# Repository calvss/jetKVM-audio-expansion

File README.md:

# JetKVM compatible audio ADC
This project takes in mic/line level audio from the 3.5mm jack and digitizes it using a Raspberry Pi Pico 2.

The audio is sent through the serial interface in a modified 48kHz 16-bit 2-channel PCM format. The audio is sent in packets of 32768 samples each, with a `0xFFFF` stop character at the end to ensure left/right channel alignment.

The JetKVM reads its serial interface from `/dev/ttyS3` and sends the raw byte packets though the network to a client PC running a python script (`test_piping.py`) that decodes the packets into a standard PCM audio stream.

## How to deploy:

Since the JetKVM doesn't ship with scp by default, we can use ssh and pipe the binary manually: `cat build/audio-client-c | ssh root@jetKVM "cat > /root/audio-client-c"`

## How to use:

On the client: `ssh root@jetkvm "/root/audio-client-c" | ffplay -fflags nobuffer -f s16le -ch_layout stereo -ar 48k -`.

# Known issues:
If you're going to fab this board design you should know the tip and sleeve contacts on the 3.5mm jack footprint are backwards.

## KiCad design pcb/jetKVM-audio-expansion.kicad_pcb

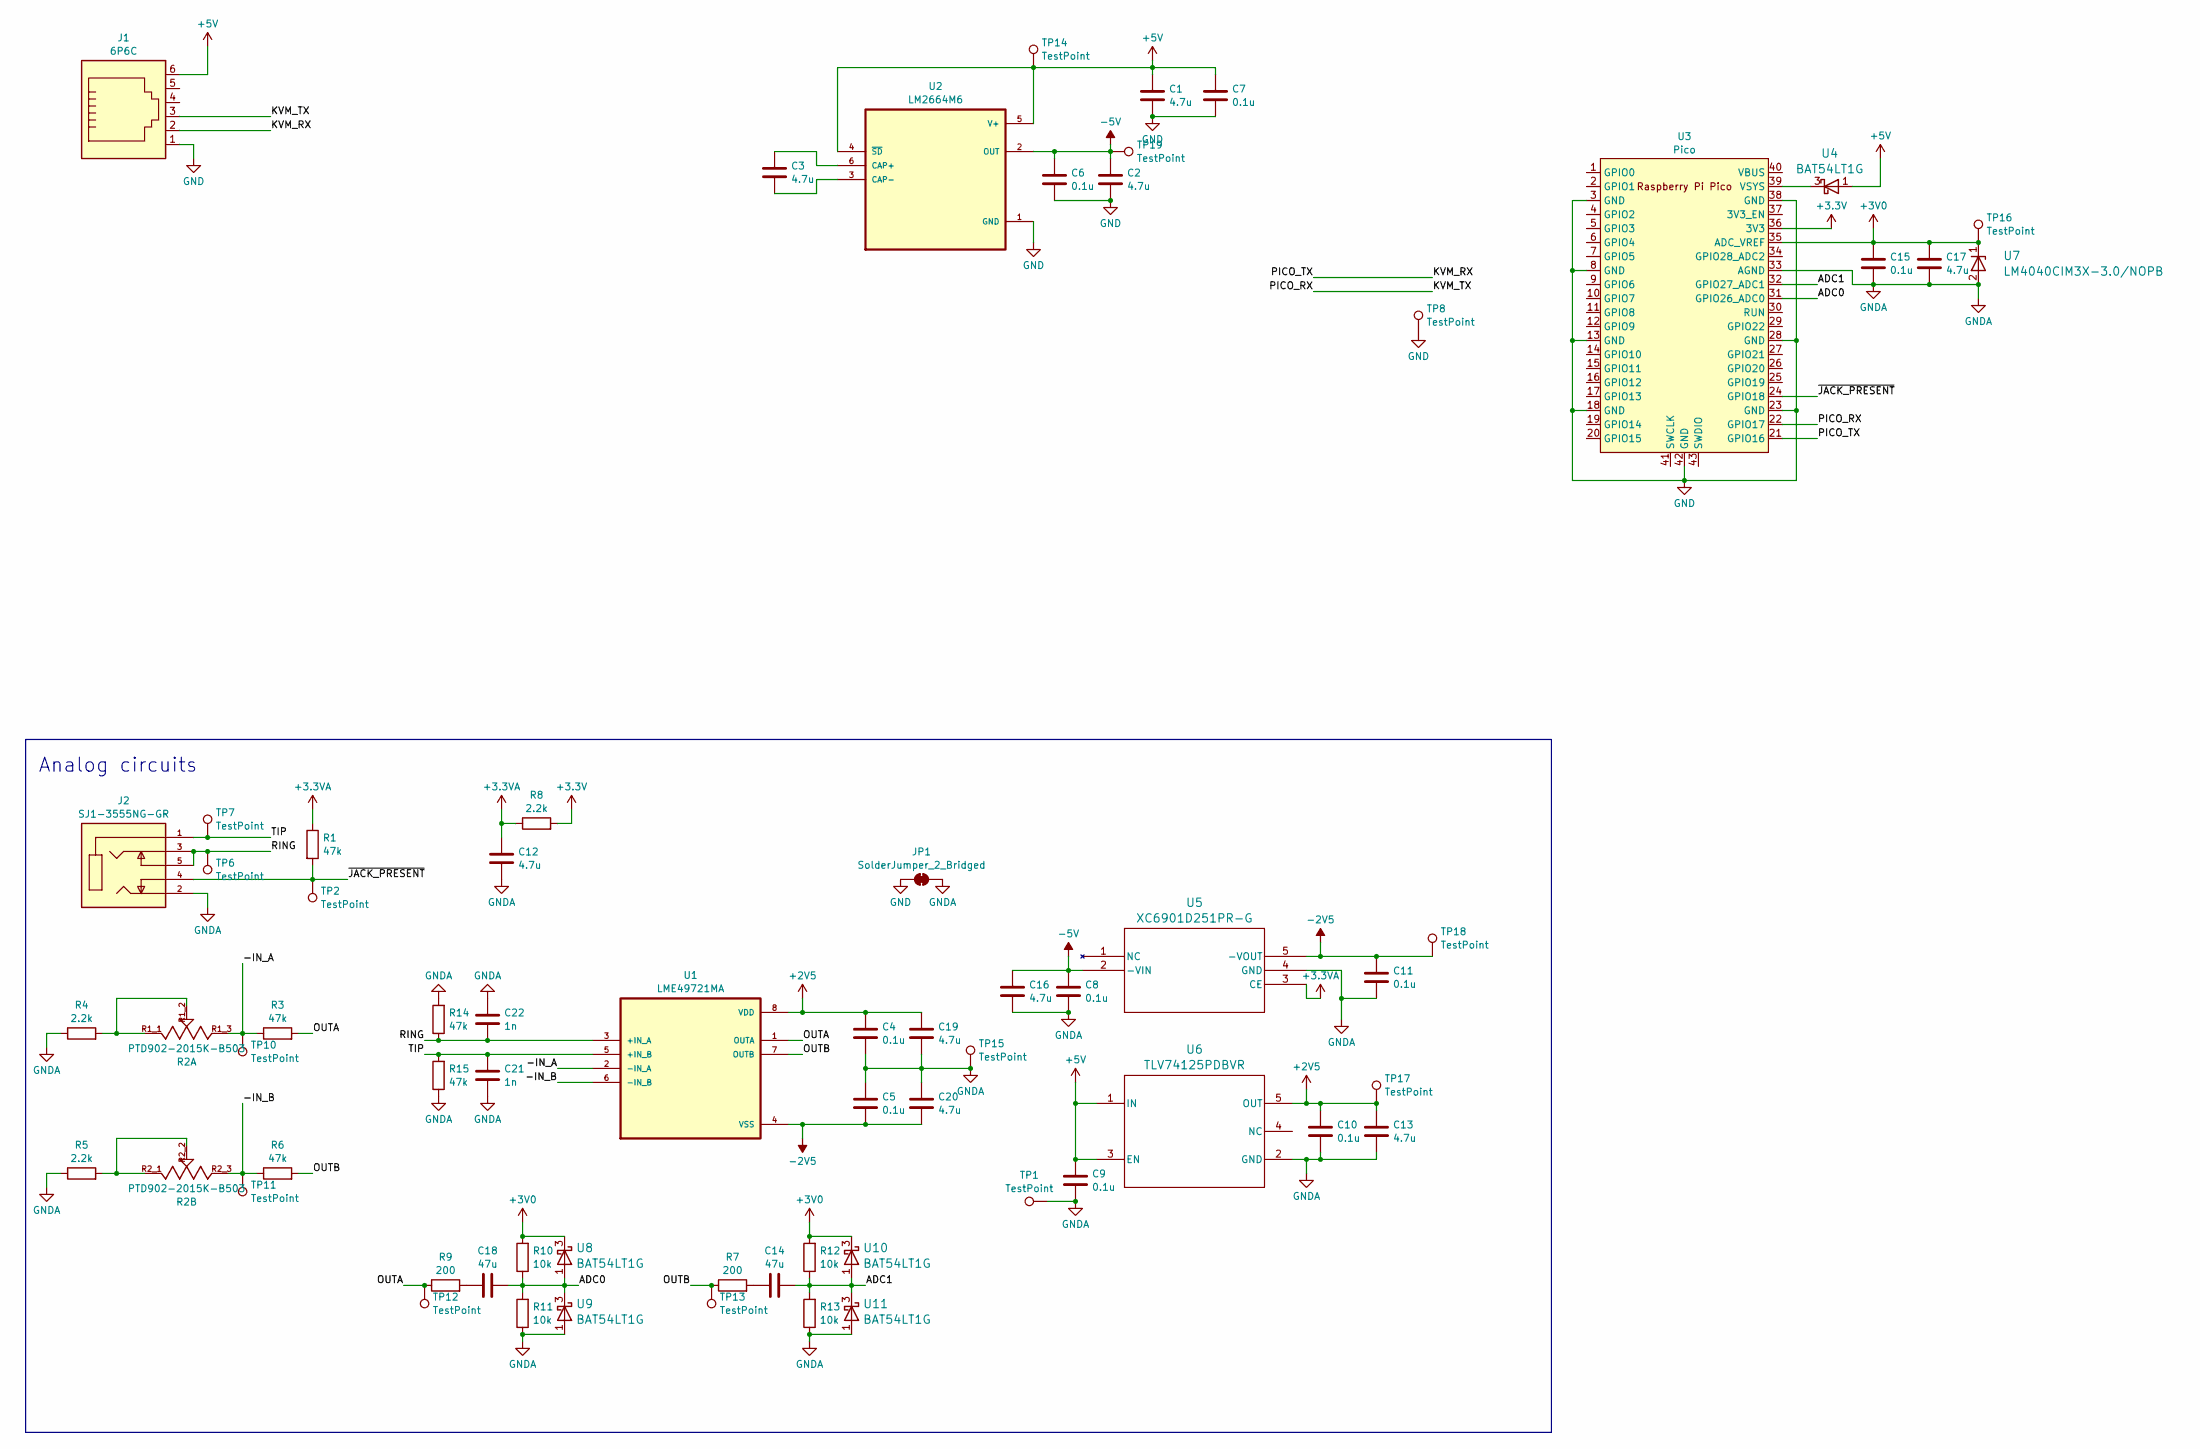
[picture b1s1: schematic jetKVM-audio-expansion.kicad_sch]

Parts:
C1, C2, C3, C12, C13, C16, C17, C19, C20: 4.7u; C_0805_2012Metric_Pad1.18x1.45mm_HandSolder
C4, C5, C6, C7, C8, C9, C10, C11, C15: 0.1u; C_0805_2012Metric_Pad1.18x1.45mm_HandSolder
C14, C18: 47u; C_0805_2012Metric_Pad1.18x1.45mm_HandSolder
C21, C22: 1n; C_0805_2012Metric_Pad1.18x1.45mm_HandSolder
J1: 6P6C; RJ25_Wayconn_MJEA-660X1_Horizontal
J2: SJ1-3555NG-GR; CUI_SJ1-3555NG-GR; PARTREV 1.02
JP1: SolderJumper_2_Bridged; SolderJumper-2_P1.3mm_Bridged2Bar_RoundedPad1.0x1.5mm
R1, R3, R6, R14, R15: 47k; R_0805_2012Metric_Pad1.20x1.40mm_HandSolder
R2: PTD902-2015K-B503; POT_PTD902-2015K-B503; PARTREV 1.0
R4, R5, R8: 2.2k; R_0805_2012Metric_Pad1.20x1.40mm_HandSolder
R7, R9: 200; R_0805_2012Metric_Pad1.20x1.40mm_HandSolder
R10, R11, R12, R13: 10k; R_0805_2012Metric_Pad1.20x1.40mm_HandSolder
TP1, TP2, TP6, TP7, TP8, TP10, TP11, TP12, TP13, TP14, TP15, TP16, TP17, TP18, TP19: TestPoint; TestPoint_Loop_D1.80mm_Drill1.0mm_Beaded
U1: LME49721MA; SOIC127P599X175-8N
U2: LM2664M6; SOT95P280X145-6N
U3: Pico; RPi_Pico_SMD_TH
U4, U8, U9, U10, U11: BAT54LT1G; SOT-23-3_1P4X3P040_ONS
U5: XC6901D251PR-G; SOT_D251PR-G_TOR
U6: TLV74125PDBVR; DBV0005A_N
U7: LM4040CIM3X-3.0/NOPB; DBZ3

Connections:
+2V5: C4.1, C10.1, C13.1, C19.1, TP17.1, U1.8 (VDD), U6.5 (OUT)
+3.3V: R8.2, U3.36 (3V3)
+3.3VA: C12.1, R1.1, R8.1, U5.3 (CE)
+3V0: C15.1, C17.1, R10.2, R12.2, TP16.1, U3.35 (ADC_VREF), U7.1, U8.3, U10.3
+5V: C1.1, C7.1, C9.1, J1.6, TP14.1, U2.4 (~SD), U2.5 (V+), U4.1, U6.1 (IN), U6.3 (EN)
-2V5: C5.2, C11.1, C20.2, TP18.1, U1.4 (VSS), U5.5 (-VOUT)
-5V: C2.1, C6.1, C8.1, C16.1, TP19.1, U2.2 (OUT), U5.2 (-VIN)
/-IN_A: R2.R1_3, R3.1, TP10.1, U1.2 (-IN_A)
/-IN_B: R2.R2_3, R6.1, TP11.1, U1.6 (-IN_B)
/ADC0: C18.2, R10.1, R11.2, U3.31 (GPIO26_ADC0), U8.1, U9.3
/ADC1: C14.2, R12.1, R13.2, U3.32 (GPIO27_ADC1), U10.1, U11.3
/KVM_RX: J1.2, U3.21 (GPIO16)
/KVM_TX: J1.3, U3.22 (GPIO17)
/OUTA: R3.2, R9.1, TP12.1, U1.1 (OUTA)
/OUTB: R6.2, R7.1, TP13.1, U1.7 (OUTB)
/RING: C22.2, J2.3, J2.5, R14.1, TP6.1, U1.3 (+IN_A)
/TIP: C21.1, J2.1, R15.2, TP7.1, U1.5 (+IN_B)
/~JACK_PRESENT: J2.4, R1.2, TP2.1, U3.24 (GPIO18)
GND: C1.2, C2.2, C6.2, C7.2, J1.1, JP1.1 (A), TP8.1, U2.1 (GND), U3.3 (GND), U3.8 (GND), U3.13 (GND), U3.18 (GND), U3.23 (GND), U3.28 (GND), U3.38 (GND), U3.42 (GND)
GNDA: C4.2, C5.1, C8.2, C9.2, C10.2, C11.2, C12.2, C13.2, C15.2, C16.2, C17.2, C19.2, C20.1, C21.2, C22.1, J2.2, JP1.2 (B), R4.1, R5.1, R11.1, R13.1, R14.2, R15.1, TP1.1, TP15.1, U3.33 (AGND), U5.4 (GND), U6.2 (GND), U7.2, U9.1, U11.1
unnamed: C14.1, R7.2
unnamed: C18.1, R9.2
unnamed: R2.R1_1, R2.R1_2, R4.2
unnamed: R2.R2_1, R2.R2_2, R5.2
unnamed: C3.1, U2.6 (CAP+)
unnamed: C3.2, U2.3 (CAP-)
unnamed: U3.39 (VSYS), U4.3

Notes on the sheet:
Analog circuits

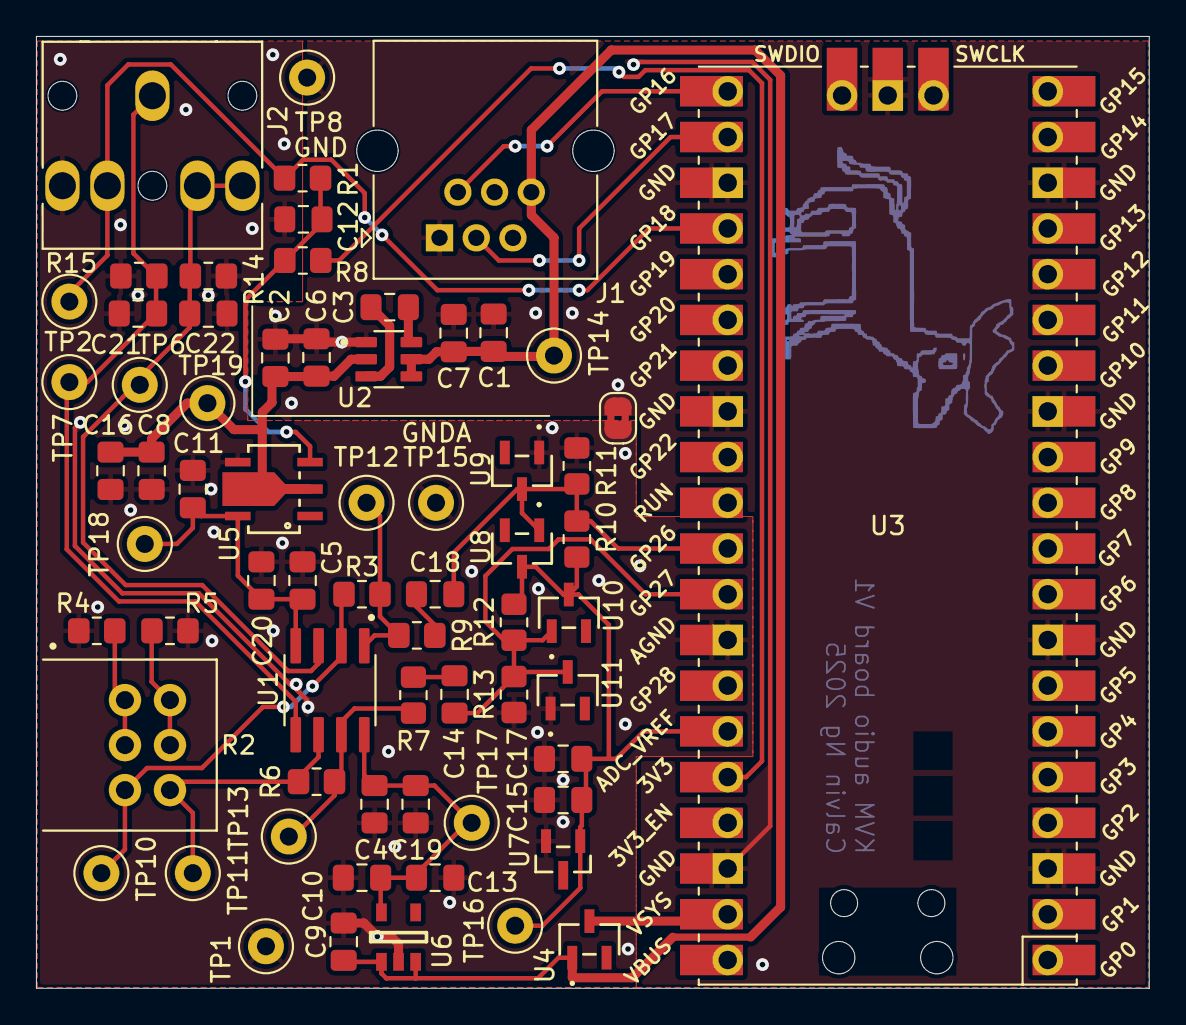
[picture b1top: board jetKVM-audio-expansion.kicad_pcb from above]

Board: 2 copper layers, 61.8 x 52.9 mm, 66 parts (0 on the bottom side), 27 nets.

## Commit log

2025-02-20 Fabbed PCB design and initial ADC code
2025-02-21 Fix IDE parser issues
2025-02-21 remove KDevelop files
2025-02-21 Change to VSCodium
2025-02-25 First try DMA
2025-03-03 Chained DMA
2025-03-04 First working proof of concept
2025-03-04 Improve comments
2025-03-05 Added exception handling to client side code
2025-03-05 Simplified code, removed useless diagnostic variables
2025-03-07 Reorganize files
2025-03-08 Initial c code for audio
2025-03-09 Working prototype using C
2025-04-01 Fixed some issues of dropping audio packets
2025-04-01 Update README.md to fix long audio latency
2025-04-01 Add preview image
2025-04-01 Actually add the image this time
